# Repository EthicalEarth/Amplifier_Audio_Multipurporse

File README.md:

# Amplifier_Audio_Multipurporse

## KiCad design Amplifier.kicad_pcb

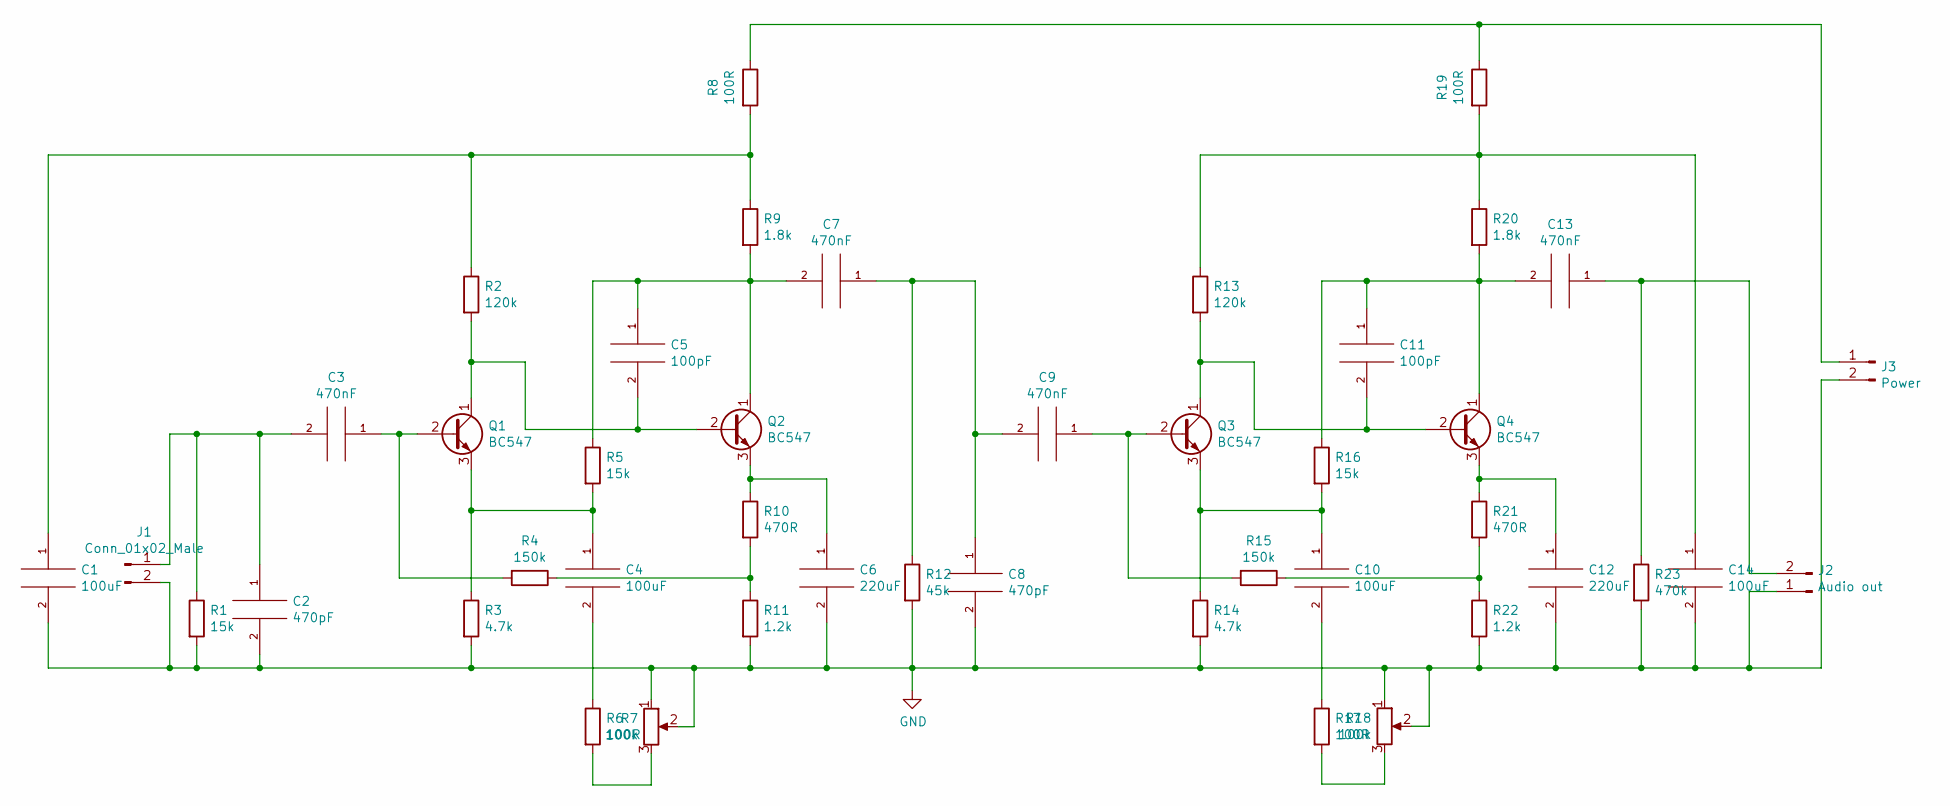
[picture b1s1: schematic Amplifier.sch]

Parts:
C1, C4, C10, C14: 100uF; C_Axial_L3.8mm_D2.6mm_P7.50mm_Horizontal
C2, C8: 470pF; C_Axial_L3.8mm_D2.6mm_P7.50mm_Horizontal
C3, C7, C9, C13: 470nF; C_Axial_L3.8mm_D2.6mm_P7.50mm_Horizontal
C5, C11: 100pF; C_Axial_L3.8mm_D2.6mm_P7.50mm_Horizontal
C6, C12: 220uF; C_Axial_L3.8mm_D2.6mm_P7.50mm_Horizontal
J1: Conn_01x02_Male; PinHeader_1x02_P2.54mm_Vertical
J2: Audio out; PinHeader_1x02_P2.54mm_Vertical
J3: Power; PinHeader_1x02_P2.54mm_Vertical
Q1, Q2, Q3, Q4: BC547; TO-92_Inline_Wide
R1, R5, R16: 15k; R_Axial_DIN0207_L6.3mm_D2.5mm_P7.62mm_Horizontal
R2, R13: 120k; R_Axial_DIN0207_L6.3mm_D2.5mm_P7.62mm_Horizontal
R3, R14: 4.7k; R_Axial_DIN0207_L6.3mm_D2.5mm_P7.62mm_Horizontal
R4, R15: 150k; R_Axial_DIN0207_L6.3mm_D2.5mm_P7.62mm_Horizontal
R6, R8, R17, R19: 100R; R_Axial_DIN0207_L6.3mm_D2.5mm_P7.62mm_Horizontal
R7, R18: 100k; Potentiometer_Bourns_3299W_Vertical
R9, R20: 1.8k; R_Axial_DIN0207_L6.3mm_D2.5mm_P7.62mm_Horizontal
R10, R21: 470R; R_Axial_DIN0207_L6.3mm_D2.5mm_P7.62mm_Horizontal
R11, R22: 1.2k; R_Axial_DIN0207_L6.3mm_D2.5mm_P7.62mm_Horizontal
R12: 45k; R_Axial_DIN0207_L6.3mm_D2.5mm_P7.62mm_Horizontal
R23: 470k; R_Axial_DIN0207_L6.3mm_D2.5mm_P7.62mm_Horizontal

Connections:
GND: C1.2, C2.2, C6.2, C8.2, C12.2, C14.2, J1.2, J2.1, J3.2, R1.2, R3.2, R7.1, R7.2, R11.2, R12.2, R14.2, R18.1, R18.2, R22.2, R23.2
unnamed: C1.1, R2.1, R8.2, R9.1
unnamed: C2.1, C3.2, J1.1, R1.1
unnamed: C3.1, Q1.2 (B), R4.2
unnamed: C4.1, Q1.3 (E), R3.1, R5.2
unnamed: C4.2, R6.1
unnamed: C5.1, C7.2, Q2.1 (C), R5.1, R9.2
unnamed: C5.2, Q1.1 (C), Q2.2 (B), R2.2
unnamed: C6.1, Q2.3 (E), R10.1
unnamed: C7.1, C8.1, C9.2, R12.1
unnamed: C9.1, Q3.2 (B), R15.2
unnamed: C10.1, Q3.3 (E), R14.1, R16.2
unnamed: C10.2, R17.1
unnamed: C11.1, C13.2, Q4.1 (C), R16.1, R20.2
unnamed: C11.2, Q3.1 (C), Q4.2 (B), R13.2
unnamed: C12.1, Q4.3 (E), R21.1
unnamed: C13.1, J2.2, R23.1
unnamed: C14.1, R13.1, R19.2, R20.1
unnamed: J3.1, R8.1, R19.1
unnamed: R6.2, R7.3
unnamed: R4.1, R10.2, R11.1
unnamed: R15.1, R21.2, R22.1
unnamed: R17.2, R18.3

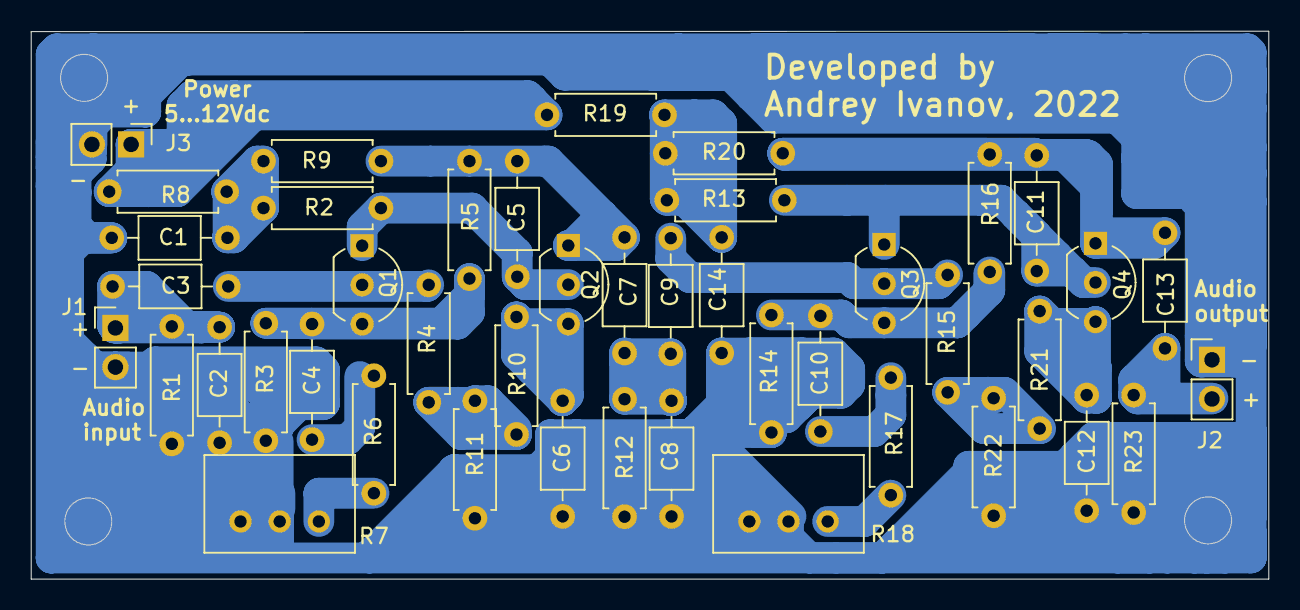
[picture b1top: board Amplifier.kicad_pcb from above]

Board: 2 copper layers, 80.3 x 35.5 mm, 44 parts (0 on the bottom side), 23 nets.
